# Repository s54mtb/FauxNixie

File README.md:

# FauxNixie
Small display module based on OLED 128x32 and 8 pin STM32G031

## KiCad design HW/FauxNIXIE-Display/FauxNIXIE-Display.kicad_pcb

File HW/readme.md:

# HARDWARE for FauxNixie project

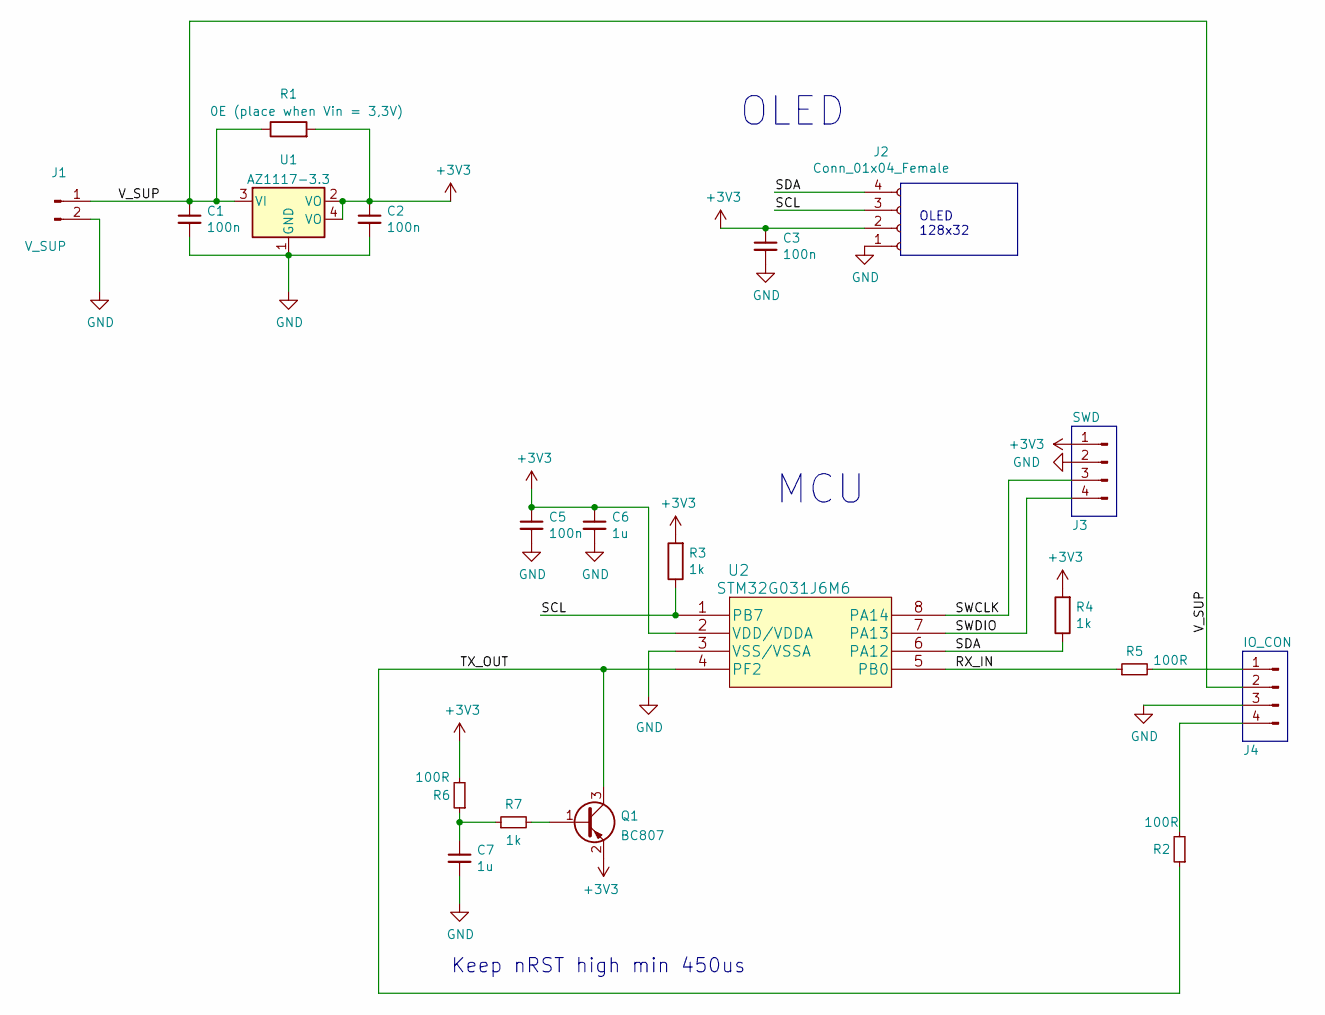
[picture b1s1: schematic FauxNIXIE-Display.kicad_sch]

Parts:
C1: 100n; C_0603_1608Metric
C2, C3, C5: 100n; C_0402_1005Metric
C6, C7: 1u; C_0402_1005Metric
J1: V_SUP; PinHeader_1x02_P2.54mm_Vertical
J2: Conn_01x04_Female; SSD1306-0.91-OLED-4pin-128x32
J3: SWD; PinHeader_1x04_P2.54mm_Vertical
J4: IO_CON; PinHeader_1x04_P2.54mm_Vertical
Q1: BC807; SOT-23
R1: 0E (place when Vin = 3,3V); R_1206_3216Metric
R2, R5, R6: 100R; R_0603_1608Metric
R3, R7: 1k; R_0603_1608Metric
R4: 1k; R_0402_1005Metric_Pad0.72x0.64mm_HandSolder
U1: AZ1117-3.3; SOT-223
U2: STM32G031J6M6; SO-8_3.9x4.9mm_P1.27mm

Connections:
+3V3: C2.1, C3.1, C5.1, C6.1, J2.2, J3.1, Q1.2 (E), R1.2, R3.2, R4.2, R6.2, U1.2 (VO), U1.4 (VO), U2.2 (VDD/VDDA)
/RX_IN: R5.1, U2.5 (PB0)
/SCL: J2.3, R3.1, U2.1 (PB7)
/SDA: J2.4, R4.1, U2.6 (PA12)
/SWCLK: J3.3, U2.8 (PA14)
/SWDIO: J3.4, U2.7 (PA13)
/TX_OUT: Q1.3 (C), R2.1, U2.4 (PF2)
/V_SUP: C1.1, J1.1, J4.2, R1.1, U1.3 (VI)
GND: C1.2, C2.2, C3.2, C5.2, C6.2, C7.2, J1.2, J2.1, J3.2, J4.3, U1.1 (GND), U2.3 (VSS/VSSA)
unnamed: C7.1, R6.1, R7.1
unnamed: J4.1, R5.2
unnamed: J4.4, R2.2
unnamed: Q1.1 (B), R7.2

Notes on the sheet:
OLED
OLED 128x32
MCU
Keep nRST high min 450us

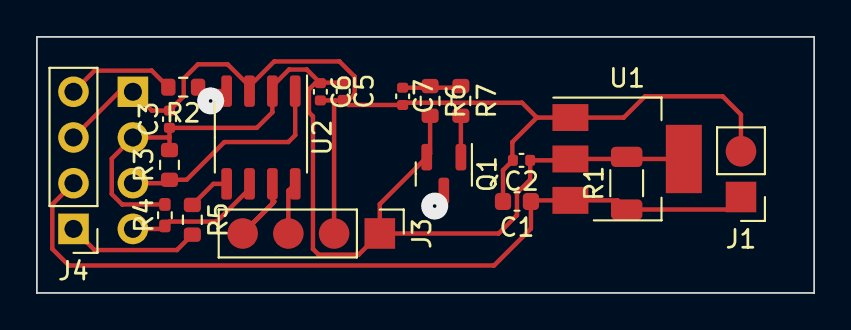
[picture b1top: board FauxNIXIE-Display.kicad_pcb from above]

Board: 2 copper layers, 43.2 x 14.2 mm, 20 parts (1 on the bottom side), 13 nets.

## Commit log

2022-04-13 Initial commit
    Hardware files, KiCad source. First prototype for tonertransfer prototyping
2022-04-13 Created readme
2022-04-13 Initial commit
    STM32G0 HAL sources
2022-04-13 Initial commit
    HAL sources
